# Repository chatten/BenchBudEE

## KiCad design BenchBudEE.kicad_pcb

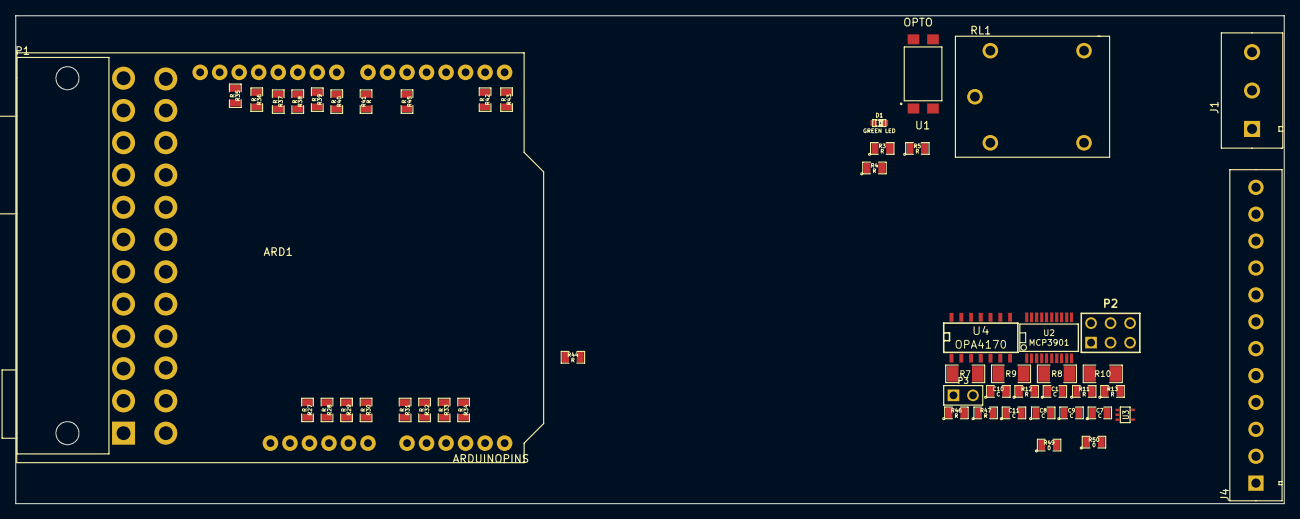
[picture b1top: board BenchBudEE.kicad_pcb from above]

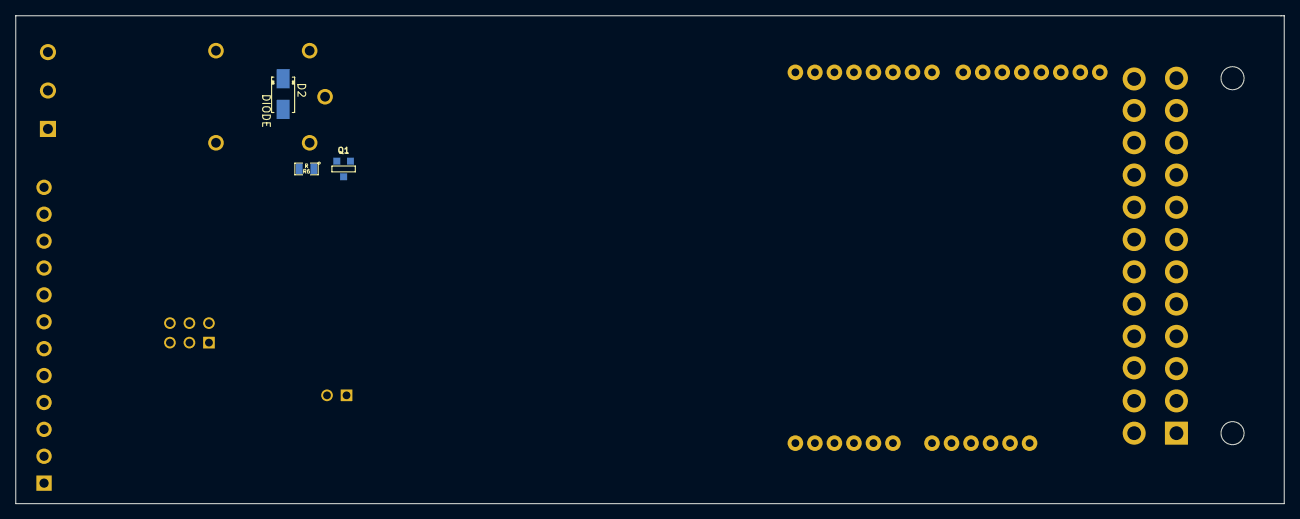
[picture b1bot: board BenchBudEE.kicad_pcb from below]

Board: 4 copper layers, 165.1 x 63.5 mm, 54 parts (3 on the bottom side), 54 nets, no tracks yet.

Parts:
ARD1: ARDUINOPINS; Arduino
C1, C7, C8, C9, C10, C11: C; SM0805
D1: GREEN LED; LED-0603
D2: DIODE; SMA-DIODE
J1: 3 Pin TB; 3pinTermBlock
J4: 12 Pin Terminal Block; 12pinTermBlock
P1: 24 Pin ATX; ATX_Header
P2: CONN_3X2; pin_array_3x2
P3: CONN_2; PIN_ARRAY_2X1
Q1: NPN; SOT23EBC
R3, R4, R5, R6, R11, R12, R13, R46, R47: R; SM0805
R7, R8, R9, R10: R; SM1206
R27, R28, R29, R30, R31, R32, R33, R34, R35, R36, R37, R38, R39, R40, R41, R42, R43, R44, R45: R; RES_SM0805
R49, R50: 0; SM0805
RL1: RELAY_SPDT; TE_SPDT
U1: OPTO; 4-SMD
U2: MCP3901; SSOP20
U3: LMT84; SOT353
U4: OPA4170; SO14E

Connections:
+5V: C8.1, C9.1, C10.1, J4.2, R27.1, U2.2, U2.3, U3.4
+12P: R3.2, R5.2, R30.1
+12V: C1.1, U4.4
-12V: C11.1, U4.11
/Arduino/ADC_CS_N: R40.2, U2.17
/Arduino/MISO: R36.2, U2.19
/Arduino/MOSI: R37.2, U2.20
/Arduino/RELAY+: R42.2, U1.1
/Arduino/SCLK: R35.2, U2.18
/Arduino/~RESET: R45.2, U2.1
/Relay/RELAY_COM: J1.2, RL1.1
/Relay/RELAY_NC: J1.3, RL1.4
/Relay/RELAY_NO: J1.1, RL1.3
/Thermocouple/CH0+: C7.1, R7.1, U2.4, U4.1
/Thermocouple/CH0-: R50.2, U2.5
/Thermocouple/CH1+: U2.7, U3.3
/Thermocouple/CH1-: R49.2, U2.6
AGND: C1.2, C7.2, C8.2, C9.2, C10.2, C11.2, R8.1, R49.1, R50.1, U2.8, U2.11, U3.1, U3.2, U3.5
GND: J4.3, J4.7, P1.3, P1.5, R28.1, R29.1, R44.1
unnamed: ARD1.24, R35.1
unnamed: ARD1.23, R36.1
unnamed: ARD1.22, R37.1
unnamed: ARD1.18, R41.1
unnamed: ARD1.19, R40.1
unnamed: ARD1.21, R38.1
unnamed: ARD1.20, R39.1
unnamed: ARD1.12, R42.1
unnamed: ARD1.6, R32.2
unnamed: ARD1.5, R31.2
unnamed: ARD1.7, R33.2
unnamed: ARD1.8, R34.2
unnamed: ARD1.3, R29.2
unnamed: ARD1.1, R27.2
unnamed: ARD1.2, R28.2
unnamed: ARD1.16, R45.1
unnamed: ARD1.4, R30.2
unnamed: ARD1.11, R43.1
unnamed: R10.2, R13.2, U4.14
unnamed: R9.2, R11.1, U4.8
unnamed: R7.2, R9.1, U4.2
unnamed: R12.2, R13.1, R46.2, R47.2, U4.13
unnamed: R8.2, R10.1, U4.3
unnamed: P2.3, R46.1
unnamed: P2.5, R47.1
unnamed: P2.1, R12.1
unnamed: P2.2, P2.4, P2.6, R11.2, U4.9
unnamed: P3.1, U2.12
unnamed: P3.2, U2.13
unnamed: Q1.2, R4.2
unnamed: Q1.1, R6.1
unnamed: R3.1, U1.4
unnamed: D2.1, Q1.3, RL1.5
unnamed: D1.1, R4.1, U1.3
unnamed: D2.2, R5.1, RL1.2

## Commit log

2014-02-02 Created Initial Blank Project Files
2014-02-03 Created a schematic skeleton
2014-02-03 Completed -Defining IO Video
    http://contextualelectronics.com/module-2/defining-your-inputs-and-outputs/
2014-02-06 Started Thermocouple Schematic -Not Complete
2014-02-10 Completed LED Driver Video + Power Module
2014-02-11 Completed Arduino Module Video
2014-02-11 Fan Module Update
2014-02-17 Started Layout Outline. Completed other schem videos
2014-02-20 started associating relay parts
2014-03-02 worked on associating parts
2014-03-02 Completed terminal block placement and footprints
2014-03-04 Completed Arduino footprint and association
